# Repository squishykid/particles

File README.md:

# Particulate and Environment Sensor

ESP8266 and ESPHome based sensor unit

## Sensors

- PMS7003 Particulate Sensor (including PM2.5)
- SenseAir S8

## Directories

- `particle_sensor_pcb` - CAD files for pcb
- `src` - ESPHome config/code

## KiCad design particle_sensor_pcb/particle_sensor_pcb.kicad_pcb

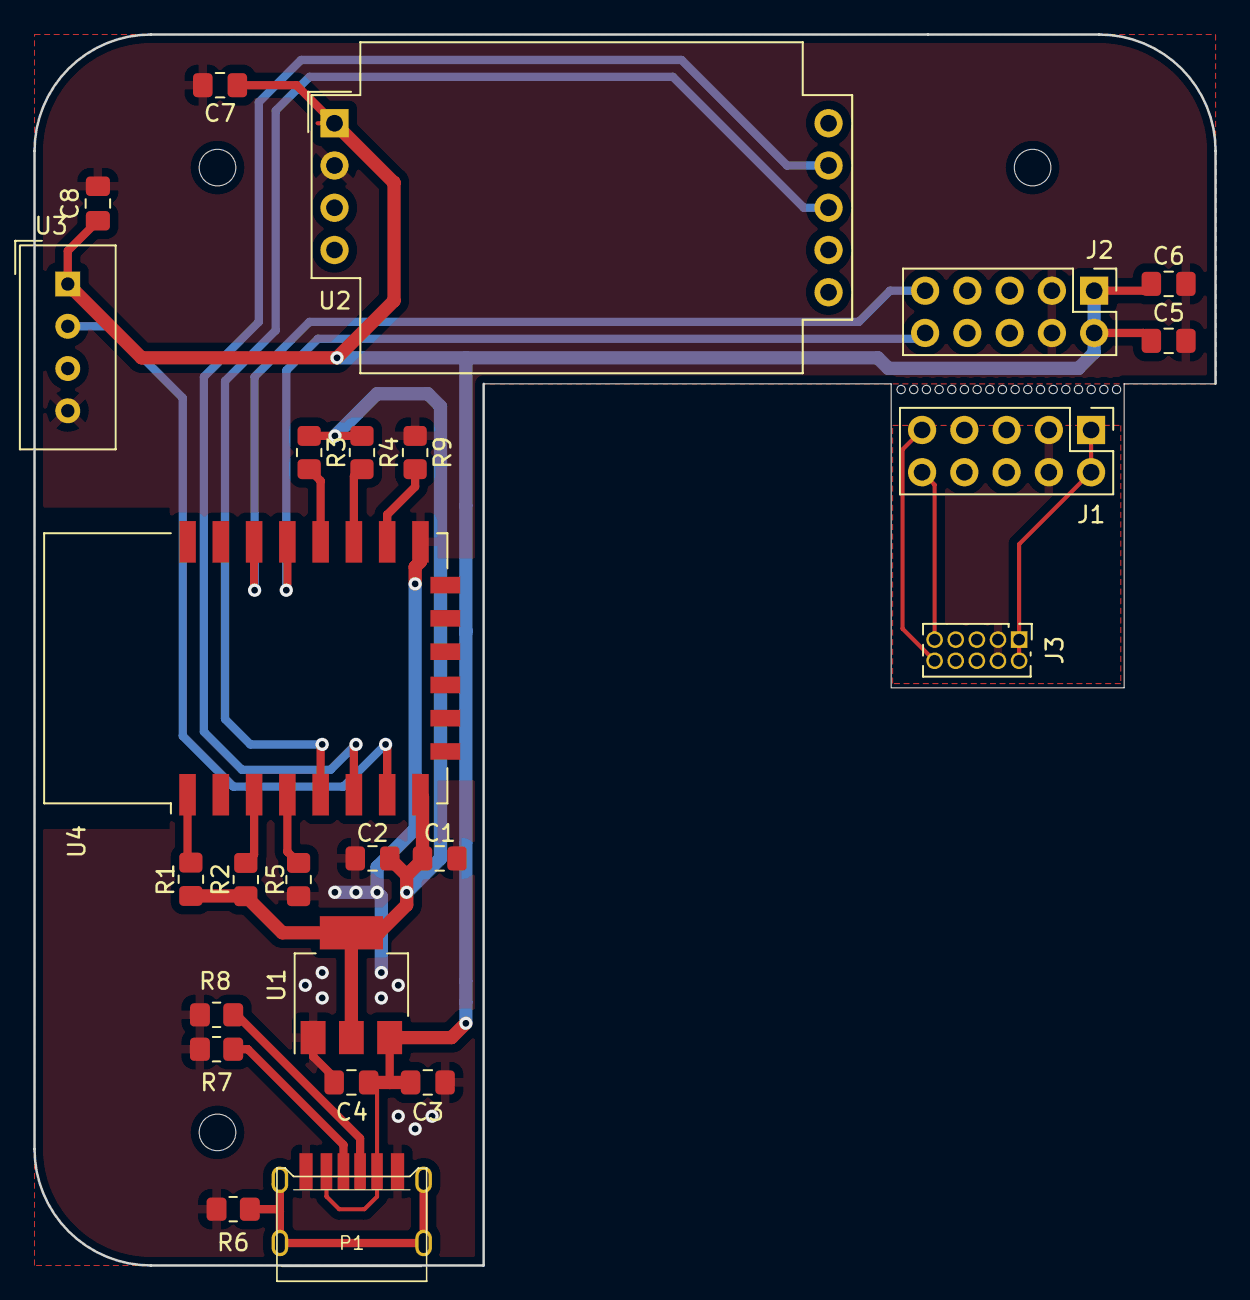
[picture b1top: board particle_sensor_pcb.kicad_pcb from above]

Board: 2 copper layers, 71.0 x 74.0 mm, 25 parts (0 on the bottom side), 21 nets.

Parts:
C1, C4: 100nF; C_0805_2012Metric_Pad1.18x1.45mm_HandSolder
C2, C3, C5, C6, C7, C8: 22uF; C_0805_2012Metric_Pad1.18x1.45mm_HandSolder
J1: DST_JUMP; PinHeader_2x05_P2.54mm_Vertical
J2: SRC_JUMP; PinHeader_2x05_P2.54mm_Vertical
J3: PMS7003; PinSocket_2x05_P1.27mm_Vertical
P1: USB_C_; TYPE-C-31-M-17_handsolder
R1, R2, R3, R4, R5, R7, R8, R9: 12K; R_0805_2012Metric_Pad1.20x1.40mm_HandSolder
R6: 1M; R_0805_2012Metric_Pad1.20x1.40mm_HandSolder
U1: AMS1117-3.3; SOT-223-3_TabPin2
U2: 004-0-0053; Senseair_S8_Up
U3: DHT11; Aosong_DHT11_5.5x12.0_P2.54mm
U4: ESP-12F; ESP-12E

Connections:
+3V3: C1.1, C2.1, R1.2, R2.2, R3.1, R4.1, U1.2 (VO), U4.8 (VCC)
+5V: C3.1, C4.1, C5.1, C6.1, C7.1, C8.1, J2.1, J2.2, P1.A9 (VBUS), P1.B9 (VBUS), U1.3 (VI), U2.1 (G+), U3.1 (VCC)
+5V_JMP: J1.1, J1.2, J3.1, J3.2
/CC1: P1.A5 (CC1), R7.2
/CC2: P1.B5 (CC2), R8.1
/SHIELD: P1.S1 (SHIELD), R6.2
D1: J2.9, U4.20 (GPIO5)
D1_JMP: J1.9, J3.10
D2: J2.10, U4.19 (GPIO4)
D2_JMP: J1.10, J3.9
D5: U2.7 (UART_TXD), U4.5 (GPIO14)
D6: U2.8 (UART_RXD), U4.6 (GPIO12)
D7: U3.2 (IO), U4.7 (GPIO13)
GND: C1.2, C2.2, C3.2, C4.2, C5.2, C6.2, C7.2, C8.2, J2.3, J2.4, P1.A12 (GND), P1.B12 (GND), R5.1, R6.1, R7.1, R8.2, R9.1, U1.1 (GND), U2.2 (G0), U3.4 (GND), U4.15 (GND)
GND_JMP: J1.3, J1.4, J3.3, J3.4
unnamed: R1.1, U4.1 (~RST)
unnamed: R2.1, U4.3 (EN)
unnamed: R3.2, U4.18 (GPIO0)
unnamed: R4.2, U4.17 (GPIO2)
unnamed: R5.2, U4.4 (GPIO16)
unnamed: R9.2, U4.16 (GPIO15)

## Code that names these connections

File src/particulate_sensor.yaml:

esphome:
  name: "particulate"
  name_add_mac_suffix: True
  platform: ESP8266
  board: d1_mini

# Enable logging
logger:

# Enable Home Assistant API
api:
  password: ""

ota:
  password: ""

wifi:
  # Enable fallback hotspot (captive portal) in case wifi connection fails
  ap:
    password: "particles"

captive_portal:
uart:
  - rx_pin: GPIO4
    baud_rate: 9600
    id: pms_uart
  - rx_pin: GPIO14
    tx_pin: GPIO12
    baud_rate: 9600
    id: sensair_uart

globals:
  - id: pm_25_measurements
    type: float[32]
    restore_value: no
  - id: pm_25_sample_count
    type: size_t
    restore_value: no
    initial_value: '0'

sensor:
  - platform: senseair
    co2:
      name: "CO₂ Concentration"
    update_interval: 60s
    uart_id: sensair_uart
  - platform: pmsx003
    type: PMSX003
    uart_id: pms_uart
    pm_1_0:
      name: "Particulate Matter <1.0µm Concentration Raw"
      id: pm_1_raw
      internal: true
    pm_2_5:
      name: "Particulate Matter <2.5µm Concentration Raw"
      id: pm_25_raw
      internal: true
      on_value:
        then:
          - lambda: |-
              if (!id(pms_warm).state) {
                return;
              }
              static bool pms_warm_previous_state;
              bool pms_warm_current_state = id(pms_warm).state;

              // reset index to 0 on edge from cold to warm
              if (pms_warm_current_state && !pms_warm_previous_state) {
                id(pm_25_sample_count) = 0;
              } else {
                id(pm_25_sample_count) += 1;
              }
              // store measurement
              id(pm_25_measurements)[id(pm_25_sample_count) % 32] = id(pm_25_raw).state;
              pms_warm_previous_state = pms_warm_current_state;
    pm_10_0:
      name: "Particulate Matter <10.0µm Concentration Raw"
      id: pm_10_raw
      internal: true

  - platform: template
    name: "Pm25"
    id: pm_25
    icon: mdi:molecule
    unit_of_measurement: "µg/m³"
    accuracy_decimals: 1

switch:
  - platform: gpio
    pin:
      number: GPIO5
      inverted: no
    id: pms_set
    name: "Particulate Matter Sensor Enabled"
    internal: true

interval:
#Controls Sleep Interval by turning on/off above switch
  - interval: 300s
    then:
      - switch.turn_on: pms_set
      - delay: 60s
      - switch.turn_off: pms_set

binary_sensor:
  - platform: template
    name: "Particulate Matter Sensor Warm"
    id: pms_warm
    internal: true
    lambda: |-
      if (id(pms_set).state) {
        return true;
      } else {
        return false;
      }
    filters:
      - delayed_on: 30s
    on_release:
      then:
        - lambda: |-
            ESP_LOGD("pm_x_calc", "Measurement collection complete. Updating synthesised sensors.");

            // PM25
            // figure out how many measurements to average
            size_t avg_over_25 = std::min(id(pm_25_sample_count), (size_t)32);
            if (avg_over_25 < 1) {
              ESP_LOGE("pm_x_calc", "did not receive any pm25 samples, is sensor reporting values?");
              id(pm_25).publish_state(NAN);
              return;
            }
            // average reading and publish to template sensor
            float sum_25 = 0.0;
            for (size_t i = 0; i < avg_over_25; i++) {
              sum_25 += id(pm_25_measurements)[i];
            }
            id(pm_25_sample_count) = 0; // reset sample count
            id(pm_25).publish_state(sum_25 / avg_over_25); // update sensor with results

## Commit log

2022-01-16 version 1.0
2022-01-16 removed temp files
2022-01-16 add esphome code
2022-01-16 docs and requirements.txt
2022-01-16 root readme
2022-10-09 add sensair s8 support
2022-10-09 update requirements
2022-10-10 Changed micro usb to Type-C port.
2022-10-23 USB-C connector, fix bodge, add jumper board
2023-05-20 remove pm1 and pm10, change icon for pm25
